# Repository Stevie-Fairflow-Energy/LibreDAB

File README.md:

# LibreDAB
An open source bi-directional Dual Active Bridge converter for connecting a Sodium Ion Battery to a 400 V DC link
Taking strong inspiration from the OwnTech microinverter: https://github.com/owntech-foundation/micro-inverter/

  Development Stage - Planning - Design has not started.

- **Manifesto**
	- The project goals are to:
		- Develop an open source bi-directional Dual Active Bridge converter for connecting a Sodium Ion Battery to a 400 V DC link.
		- Make the design repairable in itself.
		- Make the design a useful module within the context of solar PV, batteries and inverters. (e.g. a portable power station)
- **Open, for everyone, forever**
	- This project welcomes community input. With strong links to the OwnTech foundation and Fairflow Energy.
	- The collective work generated is meant to remain open.
	- Design files are made with open source software - Namely KiCAD.
- **Specifications**

Category | Requirement | Notes 
:---|:---|:---
Battery chemistry | Sodium Ion | New battery technology with abundant raw material availability 
Battery voltage range | 23.8 V - 58.8 V | 14 Series Cells of ~1.7 V to 4.2 V per cell. This enables compatibility with LibreSolar BMS C1 which sets a maximum voltage of 60 V. (https://github.com/LibreSolar/bms-c1) 
Nominal Battery Voltage | 42 V | Based on 3 V per cell 
Nominal Battery Current | 20 A | At 42 V and 800 W power transfer to DC link 
Peak Battery Current | 35.3 A | At 23.8 V and 800 W power transfer to DC link 
DC Link Voltage | 400 V | Based on a 230 V AC inverter 
Nominal DC link current | 2 A | 
Rated DC link Power | 800 W | Sufficient for a plug-in solar and storage application 
Efficiency | >95% | Target at nominal conditions 
Size | Target 70 mm x 280 mm PCB footprint | Similar size to 14 x 18650 cells next to each other 

- **Repairability**
	- Golden rules:
		- Components only placed on a single side of the PCB to allow simple rework
		- Components should be handle-able with standard tweezers (no smaller than 0402 packages)
		- Physical mounting is done with screws or other re-mountable arrangements
		- No invasive potting to enable inspection and service
		- There shall be test points available for all major power and control nets
	- Preferences:
		- Use of pin-compatible parts. e.g. a common footprint that has multiple options from different manufacturers to meet the same function
		- Minimise the number of different passive components used. e.g. parallel or series common components on the BOM where possible.
	- Notes:
		- Long-term relevance will be maintained at a whole module level. I.e. This DAB should be maintained and updated as a functional block when components used become unavailable. The physical size, mounting arrangements and connections should be maintained in future revisions.
	  
- **Control**
	- LibreDAB shall follow a bi-directional power reference. Therefore it needs to know voltage and current on both sides of the converter.
	- The reference can be delivered either as an analogue voltage signal or via serial.
	- LibreDAB shall provide a "No Error" indication, the absence of that indication should be read as an error.
   
- **Key Component Selections**
	- <100 V switch
		- TI LMG5200MOFR - 80 V, 10 A half bridge with driver
		- EPC2152 - 80 V, 15 A half bridge with driver
		- EPC23102 - 100 V, 35 A half bridge with driver - https://epc-co.com/epc/products/gan-fets-and-ics/epc23102
		- **Siliup SP010N01BGHTO 100 V 370A TOLL-8L MOSFET  https://www.lcsc.com/product-detail/C22385350.html?s_z=n_q_SP010N01BGHTO plus TI Driver UCC27211DDAR https://www.lcsc.com/product-detail/C141980.html?s_z=n_q_UCC27211DDAR**
	- . >500 V switch
		- **TI LMG2652 GaN Integrated Half Bridge and driver** 650 V, 140 mOhm - https://www.ti.com/product/LMG2652
		- Tokmas CID12N65D(TOKMAS) GaN single switch with integrated driver 650 V,  - 140 mOhm https://www.lcsc.com/product-detail/C21547657.html?s_z=n_q_C21547657&globalKeyword=C21547657
	- Controller
		- OwnTech SPIN https://www.owntech.org/spin-2/

- **Expected PCB Stackup**
	- 4 Layer FR4 insulated PCB with the following layer assignments:
		- Sig / Power 2oz
		- In.1 reference 2oz GND plane
		- Core
		- In.2 reference 2oz GND plane
		- Sig / Power 2oz
 - **Prototyping Status**
    - Prototype LV Bridge module ready for review.
    - Design in KiCAD 9.0.7
    - The LV Bridge module is a functional LV H bridge inverter to interface between the battery / BMS and the High Frequency DAB transformer. The prototype module has gate drivers on board as well as DC voltage and current measurements. The control interfaces for the gate drive signals, voltage and current measurements and 12 V and 5 V power supplies should be connected using 2.54 mm pin headers.
        - 4 Layer FR4 insulated PCB with the following layer assignments, with via stitching for power nets to maximise use of the PCB copper for power transfer:
		  - Sig / Power 1oz
		  - In.1 reference 0.5oz GND plane
		  - Core
		  - In.2 reference 0.5oz GND plane
		  - Sig / Power 1oz
    - Specifications for LV Bridge prototype module:
    
Category | Requirement | Notes 
:---|:---|:---
Battery voltage range | 23.8 V - 58.8 V | 14 Series Cells of ~1.7 V to 4.2 V per cell. This enables compatibility with LibreSolar BMS C1 which sets a maximum voltage of 60 V. (https://github.com/LibreSolar/bms-c1) 
Nominal Battery Voltage | 42 V | Based on 3 V per cell 
Nominal Battery Current | 20 A | At 42 V and 800 W power transfer to DC link 
Peak Battery Current | 35.3 A | At 23.8 V and 800 W power transfer to DC link 
Efficiency | >97% | Target at nominal conditions 
Size | 92 mm x 92 mm PCB  | Sized to mount 92 mm fan

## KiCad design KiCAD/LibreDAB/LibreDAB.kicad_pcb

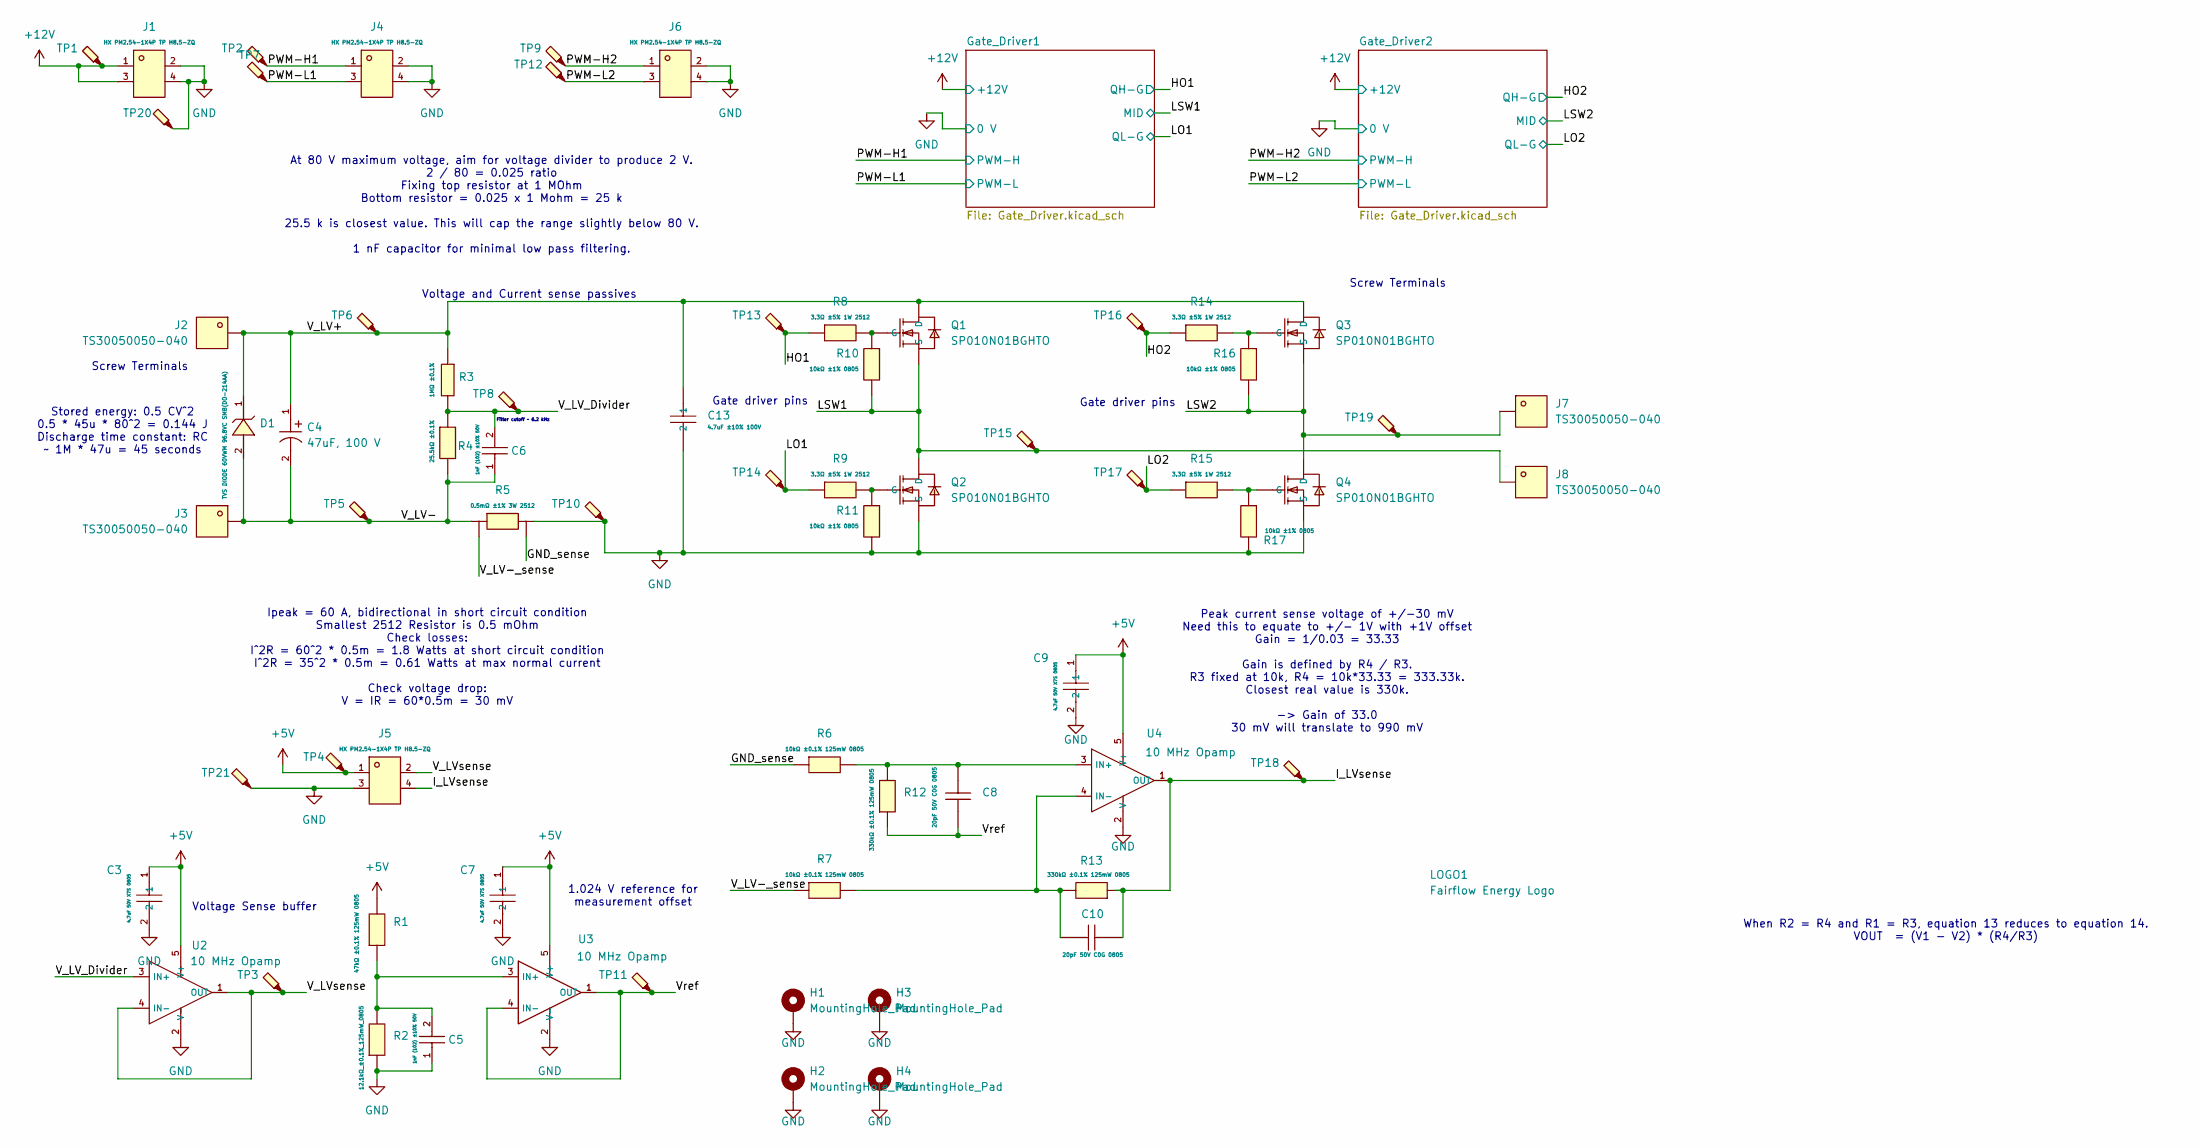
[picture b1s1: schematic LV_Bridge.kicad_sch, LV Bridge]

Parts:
C3, C7, C9: 4.7uF 50V X7S 0805; C3861036_C0805; LCSC C3861036
C4: 47uF, 100 V; C3031594_CAP-SMD_BD10_0-L10_3-W10_3-FD; LCSC C54525311
C5, C6: 1nF (102) ±10% 50V; C46653_C0805; LCSC C46653
C8, C10: 20pF 50V C0G 0805; C176292_C0805; LCSC C176292
C13: 4.7uF ±10% 100V; C41582415_C1206; LCSC C41582415
D1: TVS DIODE 60VWM 96.8VC SMB(DO-214AA); C49066953_SMB_L4_5-W3_7-LS5_4-RD; LCSC C49066953
H1, H2, H3, H4: MountingHole_Pad; MountingHole_4.3mm_M4_DIN965_Pad; LCSC C2916333
J1, J4, J5, J6: HX PM2.54-1X4P TP H8.5-ZQ; C48641754_HDR-SMD_4P-P2_54-V-F-LS4_7-R1; LCSC C48641754
J2, J3, J7, J8: TS30050050-040; C51018168_SMD_L5_0-W5_0_CON1_5X5_SMD; LCSC C51018168
LOGO1: N/A; FFE_Logo_12x12mm_Silk
Q1, Q2, Q3, Q4: SP010N01BGHTO; C22385350_TOLL-8_L10_4-W9_9-P1_20-LS11_7-BL_2; LCSC C22385350
R1: 47kΩ ±0.1% 125mW 0805; C2989281_R0805; LCSC C2989281
R2: 12.1kΩ_±0.1%_125mW_0805; C2989281_R0805; LCSC C1509644
R3: 1MΩ ±0.1%; C309662_R1206; LCSC C309662
R4: 25.5kΩ ±0.1%; C865332_R0805; LCSC C865332
R5: 0.5mΩ ±1% 3W 2512; C710260_RES-SMD_L6_4-W3_2_RLM25; LCSC C710260
R6, R7: 10kΩ ±0.1% 125mW 0805; C7431042_R0805; LCSC C7431042
R8, R9, R14, R15: 3.3Ω ±5% 1W 2512; C393074_RES-SMD_L6_4-W3_2-1; LCSC C55115149
R10, R11, R16, R17: 10kΩ ±1% 0805; C2907219_R0805; LCSC C2907219
R12, R13: 330kΩ ±0.1% 125mW 0805; C865408_R0805; LCSC C865408
TP1, TP2, TP3, TP4, TP5, TP6, TP7, TP8, TP9, TP10, TP11, TP12, TP13, TP14, TP15, TP16, TP17, TP18, TP19, TP20, TP21: TestPoint_Probe; TestPoint_Pad_D1.0mm
U2, U3, U4: 10 MHz Opamp; C398358_SOT-23-5_L3_0-W1_7-P0_95-LS2_8-BL; LCSC C398358

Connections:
+5V: C3.1, C7.1, C9.1, J5.1, R1.2, TP4.1, U2.5 (V+), U3.5 (V+), U4.5 (V+)
+12V: J1.1, J1.3, TP1.1; also elsewhere on the board
/LV_Bridge/GND_sense: R5.4 (Vsense2), R6.1
/LV_Bridge/HO1: R8.1, TP13.1; also elsewhere on the board
/LV_Bridge/HO2: R14.1, TP16.1; also elsewhere on the board
/LV_Bridge/I_LVsense: C10.2, J5.4, R13.1, TP18.1, U4.1 (OUT)
/LV_Bridge/LO1: R9.1, TP14.1; also elsewhere on the board
/LV_Bridge/LO2: R15.1, TP17.1; also elsewhere on the board
/LV_Bridge/LSW1: J8.1, Q1.2 (S), Q2.3 (D), R10.2, TP15.1; also elsewhere on the board
/LV_Bridge/LSW2: J7.1, Q3.2 (S), Q4.3 (D), R16.2, TP19.1; also elsewhere on the board
/LV_Bridge/PWM-H1: J4.1, TP2.1; also elsewhere on the board
/LV_Bridge/PWM-H2: J6.1, TP9.1; also elsewhere on the board
/LV_Bridge/PWM-L1: J4.3, TP7.1; also elsewhere on the board
/LV_Bridge/PWM-L2: J6.3, TP12.1; also elsewhere on the board
/LV_Bridge/V_LV+: C4.1, C13.1, D1.1 (K), J2.1, Q1.3 (D), Q3.3 (D), R3.1, TP6.1
/LV_Bridge/V_LV-: C4.2, C6.1, D1.2 (A), J3.1, R4.2, R5.1, TP5.1
/LV_Bridge/V_LV-_sense: R5.3 (Vsense1), R7.1
/LV_Bridge/V_LV_Divider: C6.2, R3.2, R4.1, TP8.1, U2.3 (IN+)
/LV_Bridge/V_LVsense: J5.2, TP3.1, U2.1 (OUT), U2.4 (IN-)
/LV_Bridge/Vref: C8.2, R12.1, TP11.1, U3.1 (OUT), U3.4 (IN-)
GND: C3.2, C5.1, C7.2, C9.2, C13.2, H1.1, H2.1, H3.1, H4.1, J1.2, J1.4, J4.2, J4.4, J5.3, J6.2, J6.4, Q2.2 (S), Q4.2 (S), R2.1, R5.2, R11.2, R17.2, TP10.1, TP20.1, TP21.1, U2.2 (V-), U3.2 (V-), U4.2 (V-); also elsewhere on the board
unnamed: Q1.1 (G), R8.2, R10.1
unnamed: Q2.1 (G), R9.2, R11.1
unnamed: Q3.1 (G), R14.2, R16.1
unnamed: Q4.1 (G), R15.2, R17.1
unnamed: C5.2, R1.1, R2.2, U3.3 (IN+)
unnamed: C8.1, R6.2, R12.2, U4.3 (IN+)
unnamed: C10.1, R7.2, R13.2, U4.4 (IN-)

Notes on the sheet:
Gate driver pins
At 80 V maximum voltage, aim for voltage divider to produce 2 V. 2 / 80 = 0.025 ratio Fixing top resistor at 1 MOhm Bottom resistor = 0.025 x 1 Mohm = 25 k 25.5 k is closest value. This will cap the range slightly below 80 V. 1 nF capacitor for minimal low pass filtering.
Screw Terminals
Stored energy: 0.5 CV^2 0.5 * 45u * 80^2 = 0.144 J Discharge time constant: RC ~ 1M * 47u = 45 seconds
Voltage Sense buffer
1.024 V reference for measurement offset
When R2 = R4 and R1 = R3, equation 13 reduces to equation 14. VOUT = (V1 - V2) * (R4/R3)
Peak current sense voltage of +/-30 mV Need this to equate to +/- 1V with +1V offset Gain = 1/0.03 = 33.33 Gain is defined by R4 / R3. R3 fixed at 10k, R4 = 10k*33.33 = 333.33k. Closest real value is 330k. -> Gain of 33.0 30 mV will translate to 990 mV
Ipeak = 60 A, bidirectional in short circuit condition Smallest 2512 Resistor is 0.5 mOhm Check losses: I^2R = 60^2 * 0.5m = 1.8 Watts at short circuit condition I^2R = 35^2 * 0.5m = 0.61 Watts at max normal current Check voltage drop: V = IR = 60*0.5m = 30 mV
Voltage and Current sense passives
Filter cutoff ~ 6.2 kHz

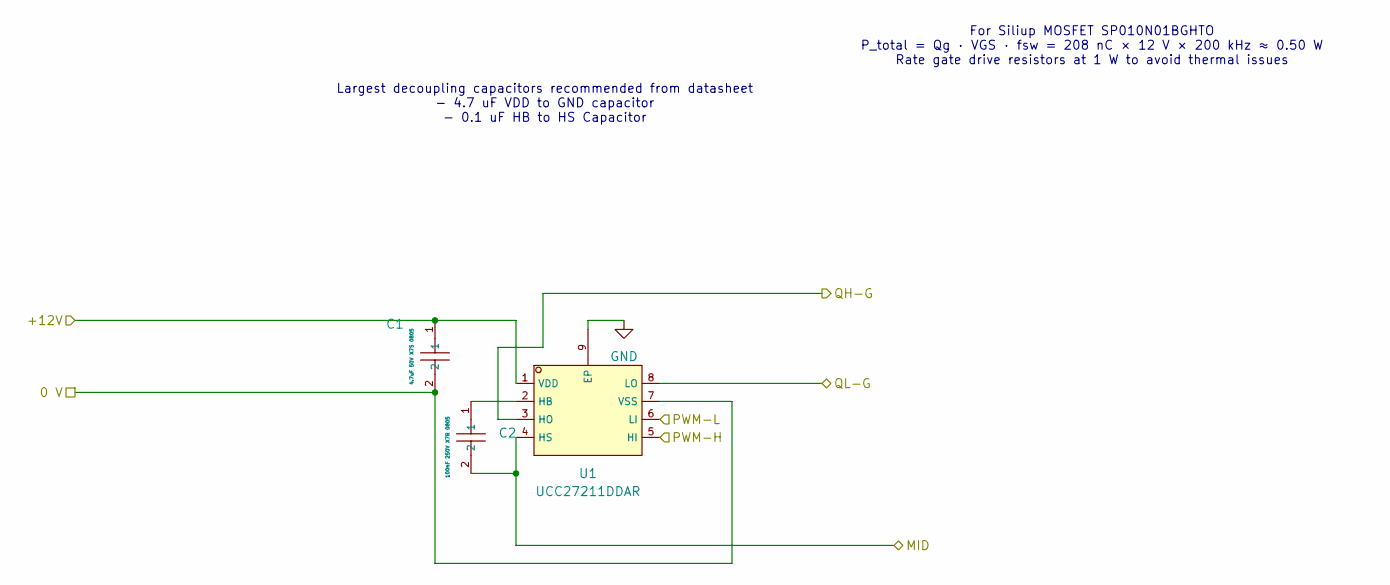
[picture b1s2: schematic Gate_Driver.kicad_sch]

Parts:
C1: 4.7uF 50V X7S 0805; C3861036_C0805; LCSC C3861036
C2: 100nF 250V X7R 0805; C5182461_C0805; LCSC C5182461
U1: UCC27211DDAR; C141980_SOIC-8_L4_9-W3_9-P1_27-LS6_0-BL-EP; LCSC C141980

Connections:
+12V: C1.1, U1.1 (VDD); also elsewhere on the board
/LV_Bridge/HO1: U1.3 (HO); also elsewhere on the board
/LV_Bridge/LO1: U1.8 (LO); also elsewhere on the board
/LV_Bridge/LSW1: C2.2, U1.4 (HS); also elsewhere on the board
/LV_Bridge/PWM-H1: U1.5 (HI); also elsewhere on the board
/LV_Bridge/PWM-L1: U1.6 (LI); also elsewhere on the board
GND: C1.2, U1.7 (VSS), U1.9 (EP); also elsewhere on the board
unnamed: C2.1, U1.2 (HB)

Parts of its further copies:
C11: 4.7uF 50V X7S 0805; C3861036_C0805; LCSC C3861036
C12: 100nF 250V X7R 0805; C5182461_C0805; LCSC C5182461
U5: UCC27211DDAR; C141980_SOIC-8_L4_9-W3_9-P1_27-LS6_0-BL-EP; LCSC C141980

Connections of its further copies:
+12V: C11.1, U5.1 (VDD); also elsewhere on the board
/LV_Bridge/HO2: U5.3 (HO); also elsewhere on the board
/LV_Bridge/LO2: U5.8 (LO); also elsewhere on the board
/LV_Bridge/LSW2: C12.2, U5.4 (HS); also elsewhere on the board
/LV_Bridge/PWM-H2: U5.5 (HI); also elsewhere on the board
/LV_Bridge/PWM-L2: U5.6 (LI); also elsewhere on the board
GND: C11.2, U5.7 (VSS), U5.9 (EP); also elsewhere on the board
unnamed: C12.1, U5.2 (HB)

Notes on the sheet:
Largest decoupling capacitors recommended from datasheet - 4.7 uF VDD to GND capacitor - 0.1 uF HB to HS Capacitor
For Siliup MOSFET SP010N01BGHTO P_total = Qg · VGS · fsw = 208 nC × 12 V × 200 kHz ≈ 0.50 W Rate gate drive resistors at 1 W to avoid thermal issues

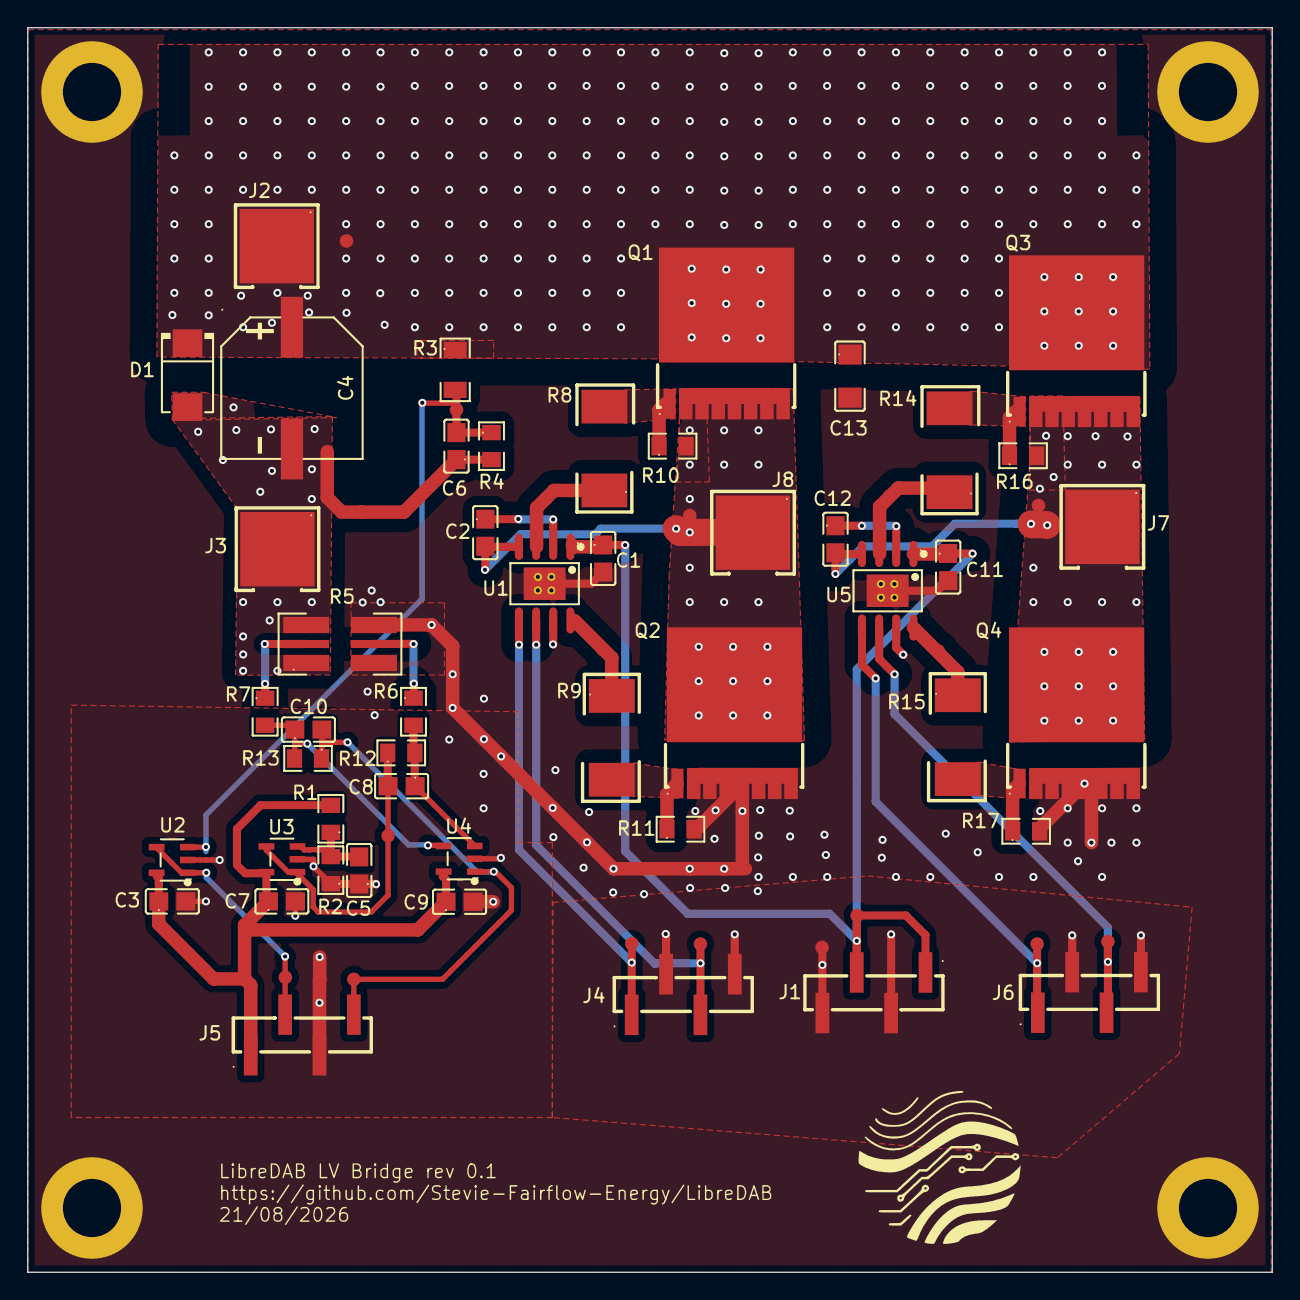
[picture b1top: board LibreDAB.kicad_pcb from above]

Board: 4 copper layers, 92.0 x 92.0 mm, 74 parts (0 on the bottom side), 30 nets.

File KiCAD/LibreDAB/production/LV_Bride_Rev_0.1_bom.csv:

Designator,Footprint,Quantity,Value,LCSC Part #
"C1, C11, C3, C7, C9",C3861036_C0805,5,4.7uF 50V X7S 0805,C3861036
"C10, C8",C176292_C0805,2,20pF 50V C0G 0805,C176292
"C12, C2",C5182461_C0805,2,100nF 250V X7R 0805,C5182461
C4,C3031594_CAP-SMD_BD10_0-L10_3-W10_3-FD,1,"47uF, 80 V",C3031594
"C5, C6",C46653_C0805,2,1nF (102) ±10% 50V,C46653
D1,C49066953_SMB_L4_5-W3_7-LS5_4-RD,1,TVS DIODE 60VWM 96.8VC SMB(DO-214AA),C49066953
"H1, H2, H3, H4",MountingHole_Pad_SMD_BD5.6-D4.1,4,MountingHole_Pad,C2916333
"J1, J4, J5, J6",C48641754_HDR-SMD_4P-P2_54-V-F-LS4_7-R1,4,HX PM2.54-1X4P TP H8.5-ZQ,C48641754
"J2, J3, J7, J8",C51018168_SMD_L5_0-W5_0_CON1_5X5_SMD,4,TS30050050-040,C51018168
LOGO1,FFE_Logo_12x12mm_Silk,1,N/A,
"Q1, Q2, Q3, Q4",C22385350_TOLL-8_L10_4-W9_9-P1_20-LS11_7-BL_2,4,SP010N01BGHTO,C22385350
R1,C2989281_R0805,1,47kΩ ±0.1% 125mW 0805,C2989281
"R10, R11, R16, R17",C2907219_R0805,4,10kΩ ±1% 0805,C2907219
"R12, R13",C865408_R0805,2,330kΩ ±0.1% 125mW 0805,C865408
"R14, R15, R8, R9",C393074_RES-SMD_L6_4-W3_2-1,4,3.3Ω ±5% 1W 2512,C393074
R2,C2989281_R0805,1,12.1kΩ_±0.1%_125mW_0805,C2989281
R3,C17514_R0805,1,1MΩ (1004) ±1%,C17514
R4,C46670_R0805,1,25.5KΩ (2552) ±1%,C46670
R5,C710260_RES-SMD_L6_4-W3_2_RLM25,1,0.5mΩ ±1% 3W 2512,C710260
"R6, R7",C7431042_R0805,2,10kΩ ±0.1% 125mW 0805,C7431042
"TP1, TP10, TP11, TP12, TP13, TP14, TP15, TP16, TP17, TP18, TP19, TP2, TP20, TP21, TP3, TP4, TP5, TP6, TP7, TP8, TP9",TestPoint_Pad_D1.0mm,21,TestPoint_Probe,
"U1, U5",C141980_SOIC-8_L4_9-W3_9-P1_27-LS6_0-BL-EP,2,UCC27211DDAR,C141980
"U2, U3, U4",C398358_SOT-23-5_L3_0-W1_7-P0_95-LS2_8-BL,3,10 MHz Opamp,C398358

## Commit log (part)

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2026-06-09 Added draft design notes
    Draft design notes using EPC and TI half bridge drivers, and a custom RM12 transformer
2026-06-09 uVerter copy as KiCad starting point
2026-06-09 Initial kicad schematic draft
2026-06-10 Schematic updates still setting up
